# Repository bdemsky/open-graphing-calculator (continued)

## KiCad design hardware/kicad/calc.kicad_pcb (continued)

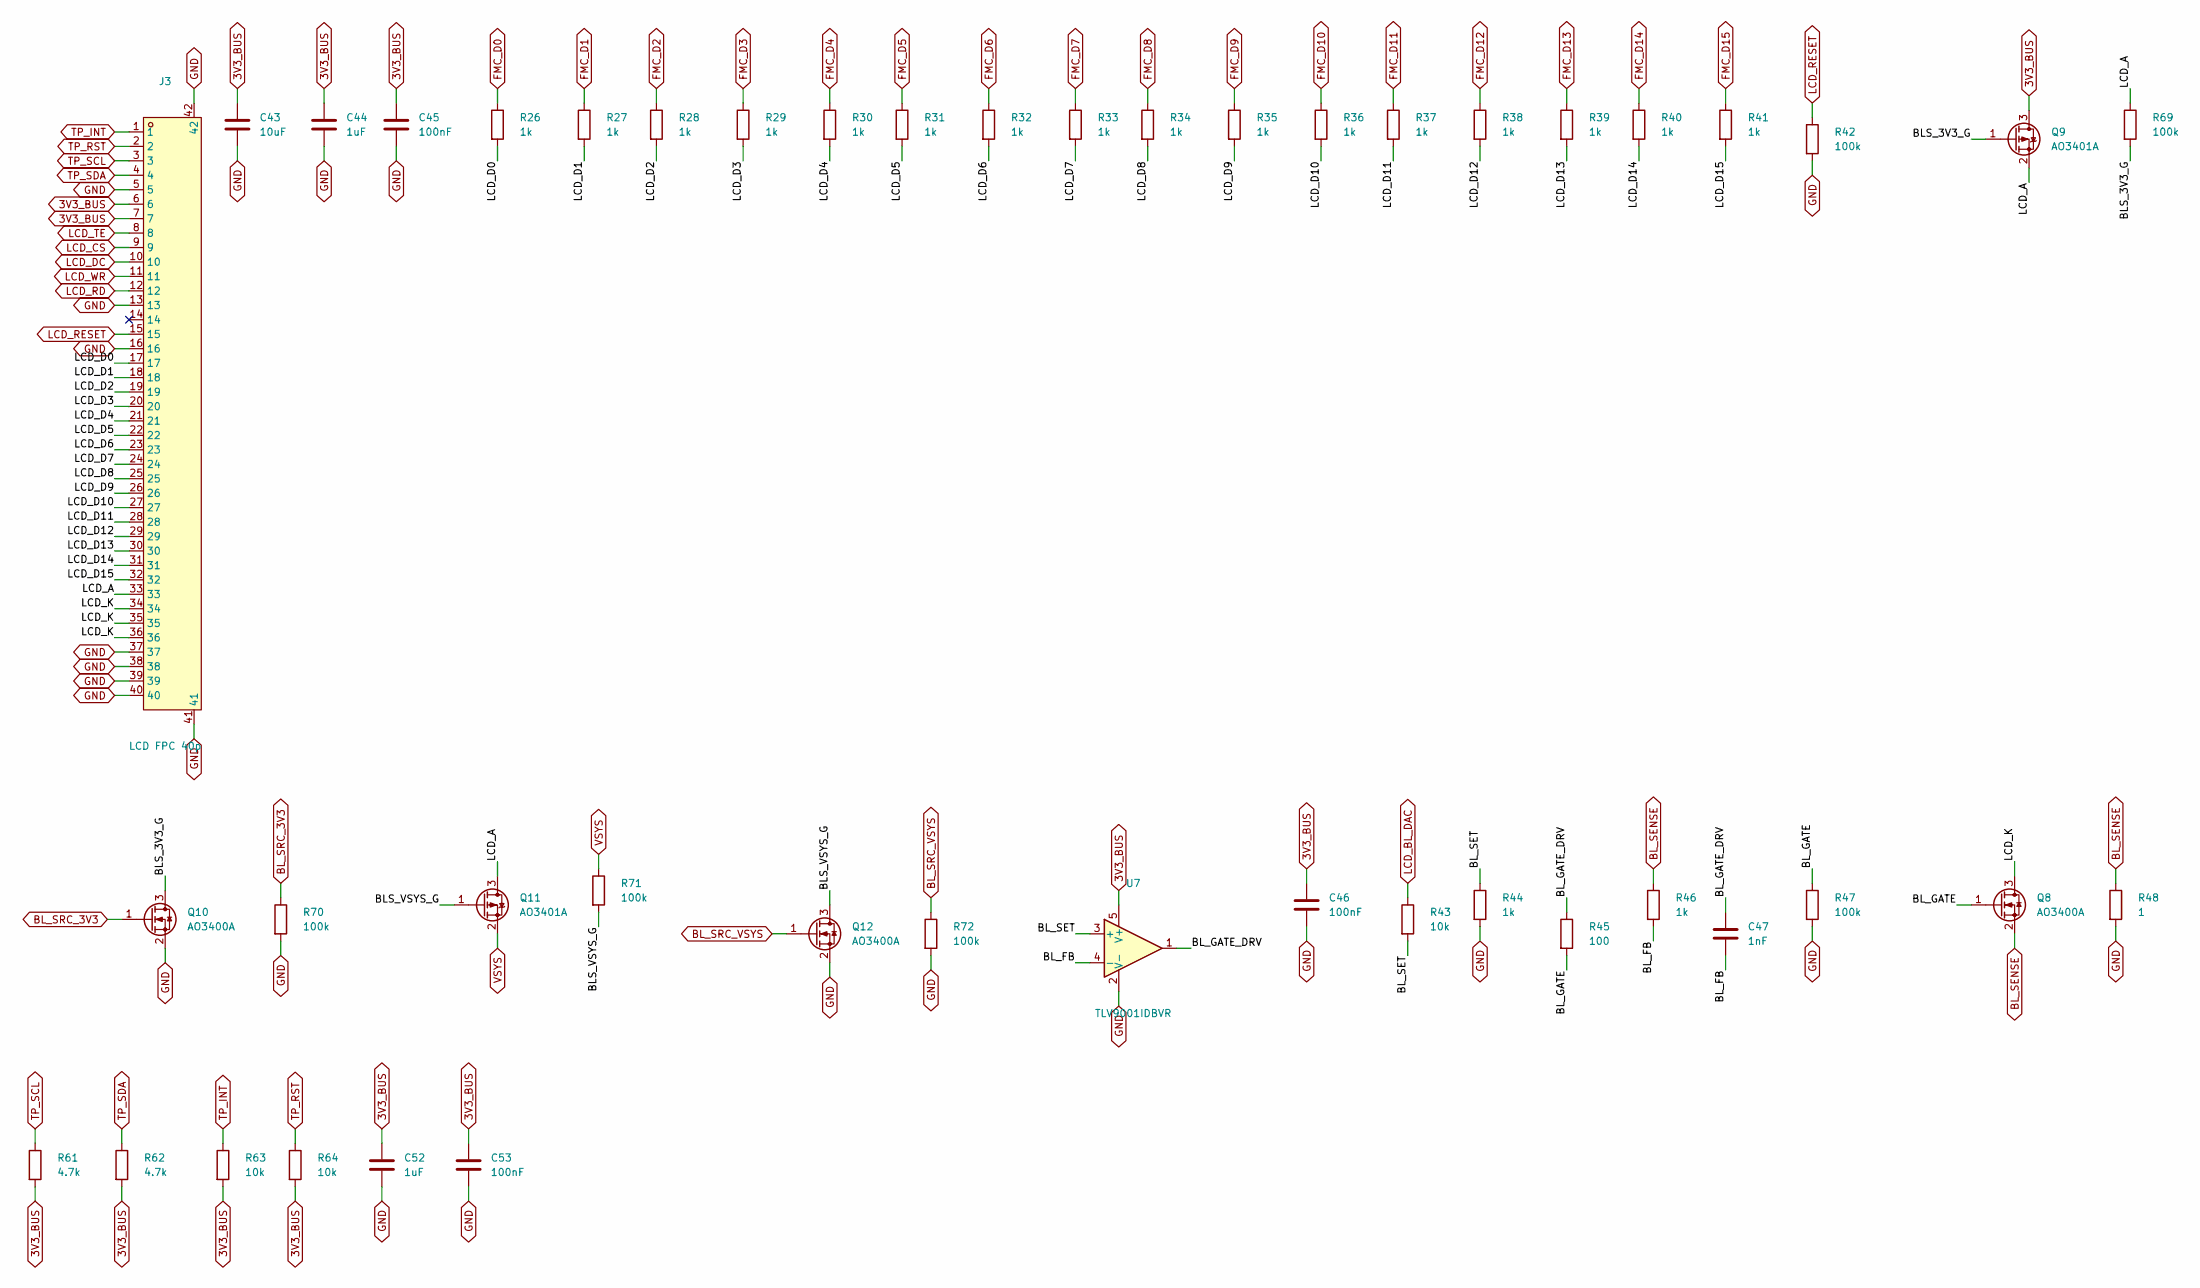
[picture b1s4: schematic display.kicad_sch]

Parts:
C43: 10uF; C_0603_1608Metric; LCSC C19702
C44, C52: 1uF; C_0402_1005Metric; LCSC C52923
C45, C46, C53: 100nF; C_0402_1005Metric; LCSC C307331
C47: 1nF; C_0402_1005Metric; LCSC C1523
J3: LCD FPC 40p; FPC-SMD_P0.50-40P_QCHF-SM-H2.0; LCSC C262686
Q8, Q10, Q12: AO3400A; SOT-23; LCSC C20917
Q9, Q11: AO3401A; SOT-23; LCSC C15127
R26, R27, R28, R29, R30, R31, R32, R33, R34, R35, R36, R37, R38, R39, R40, R41, R44, R46: 1k; R_0402_1005Metric; LCSC C11702
R42, R47, R69, R70, R71, R72: 100k; R_0402_1005Metric; LCSC C25741
R43, R63, R64: 10k; R_0402_1005Metric; LCSC C25744
R45: 100; R_0402_1005Metric; LCSC C25076
R48: 1; R_0603_1608Metric; LCSC C22936
R61, R62: 4.7k; R_0402_1005Metric; LCSC C25900
U7: TLV9001IDBVR; SOT-23-5; LCSC C398363

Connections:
3V3_BUS: C43.1, C44.1, C45.1, C46.1, C52.1, C53.1, J3.6, J3.7, Q9.3 (D), R61.2, R62.2, R63.2, R64.2, U7.5 (V+); also elsewhere on the board
/Display/BLS_3V3_G: Q9.1 (G), Q10.3 (D), R69.2
/Display/BLS_VSYS_G: Q11.1 (G), Q12.3 (D), R71.2
/Display/BL_FB: C47.2, R46.2, U7.4 (-)
/Display/BL_GATE: Q8.1 (G), R45.2, R47.1
/Display/BL_GATE_DRV: C47.1, R45.1, U7.1
/Display/BL_SET: R43.2, R44.1, U7.3 (+)
/Display/LCD_A: J3.33, Q9.2 (S), Q11.3 (D), R69.1
/Display/LCD_D0: J3.17, R26.2
/Display/LCD_D1: J3.18, R27.2
/Display/LCD_D2: J3.19, R28.2
/Display/LCD_D3: J3.20, R29.2
/Display/LCD_D4: J3.21, R30.2
/Display/LCD_D5: J3.22, R31.2
/Display/LCD_D6: J3.23, R32.2
/Display/LCD_D7: J3.24, R33.2
/Display/LCD_D8: J3.25, R34.2
/Display/LCD_D9: J3.26, R35.2
/Display/LCD_D10: J3.27, R36.2
/Display/LCD_D11: J3.28, R37.2
/Display/LCD_D12: J3.29, R38.2
/Display/LCD_D13: J3.30, R39.2
/Display/LCD_D14: J3.31, R40.2
/Display/LCD_D15: J3.32, R41.2
/Display/LCD_K: J3.34, J3.35, J3.36, Q8.3 (D)
BL_SENSE: Q8.2 (S), R46.1, R48.1; also elsewhere on the board
BL_SRC_3V3: Q10.1 (G), R70.1; also elsewhere on the board
BL_SRC_VSYS: Q12.1 (G), R72.1; also elsewhere on the board
FMC_D0: R26.1; also elsewhere on the board
FMC_D1: R27.1; also elsewhere on the board
FMC_D2: R28.1; also elsewhere on the board
FMC_D3: R29.1; also elsewhere on the board
FMC_D4: R30.1; also elsewhere on the board
FMC_D5: R31.1; also elsewhere on the board
FMC_D6: R32.1; also elsewhere on the board
FMC_D7: R33.1; also elsewhere on the board
FMC_D8: R34.1; also elsewhere on the board
FMC_D9: R35.1; also elsewhere on the board
FMC_D10: R36.1; also elsewhere on the board
FMC_D11: R37.1; also elsewhere on the board
FMC_D12: R38.1; also elsewhere on the board
FMC_D13: R39.1; also elsewhere on the board
FMC_D14: R40.1; also elsewhere on the board
FMC_D15: R41.1; also elsewhere on the board
GND: C43.2, C44.2, C45.2, C46.2, C52.2, C53.2, J3.5, J3.13, J3.16, J3.37, J3.38, J3.39, J3.40, J3.41, J3.42, Q10.2 (S), Q12.2 (S), R42.2, R44.2, R47.2, R48.2, R70.2, R72.2, U7.2 (V-); also elsewhere on the board
LCD_BL_DAC: R43.1; also elsewhere on the board
LCD_CS: J3.9; also elsewhere on the board
LCD_DC: J3.10; also elsewhere on the board
LCD_RD: J3.12; also elsewhere on the board
LCD_RESET: J3.15, R42.1; also elsewhere on the board
LCD_TE: J3.8; also elsewhere on the board
LCD_WR: J3.11; also elsewhere on the board
TP_INT: J3.1, R63.1; also elsewhere on the board
TP_RST: J3.2, R64.1; also elsewhere on the board
TP_SCL: J3.3, R61.1; also elsewhere on the board
TP_SDA: J3.4, R62.1; also elsewhere on the board
VSYS: Q11.2 (S), R71.1; also elsewhere on the board

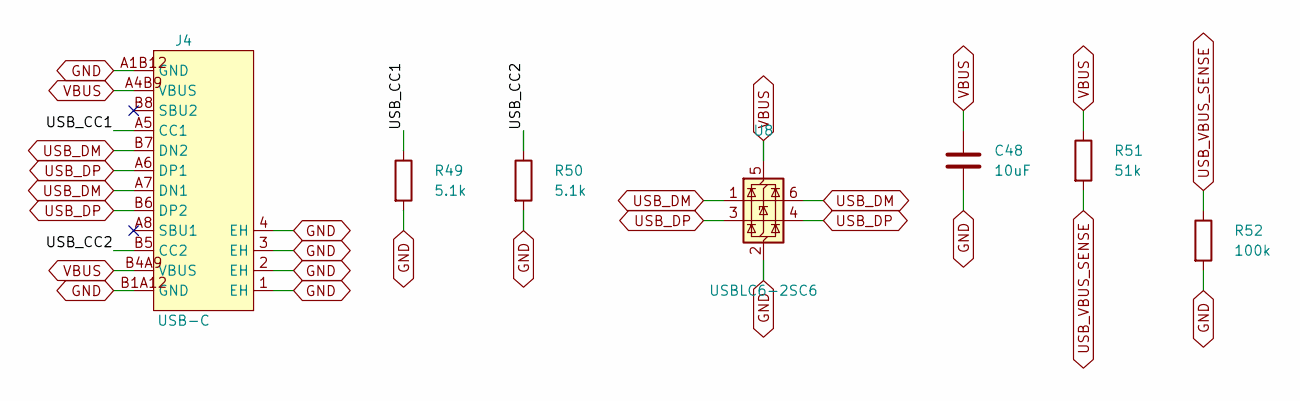
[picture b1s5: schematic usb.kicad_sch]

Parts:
C48: 10uF; C_0603_1608Metric; LCSC C96446
J4: USB-C; USB-C_SMD-TYPE-C-31-M-12_1; LCSC C165948
R49, R50: 5.1k; R_0402_1005Metric; LCSC C25905
R51: 51k; R_0402_1005Metric; LCSC C25794
R52: 100k; R_0402_1005Metric; LCSC C25741
U8: USBLC6-2SC6; SOT-23-6; LCSC C7519

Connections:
/USB/USB_CC1: J4.A5 (CC1), R49.1
/USB/USB_CC2: J4.B5 (CC2), R50.1
GND: C48.2, J4.1 (EH), J4.2 (EH), J4.3 (EH), J4.4 (EH), J4.A1B12 (GND), J4.B1A12 (GND), R49.2, R50.2, R52.2, U8.2 (GND); also elsewhere on the board
USB_DM: J4.A7 (DN1), J4.B7 (DN2), U8.1 (I/O1), U8.6 (I/O1); also elsewhere on the board
USB_DP: J4.A6 (DP1), J4.B6 (DP2), U8.3 (I/O2), U8.4 (I/O2); also elsewhere on the board
USB_VBUS_SENSE: R51.2, R52.1; also elsewhere on the board
VBUS: C48.1, J4.A4B9 (VBUS), J4.B4A9 (VBUS), R51.1, U8.5 (VBUS); also elsewhere on the board

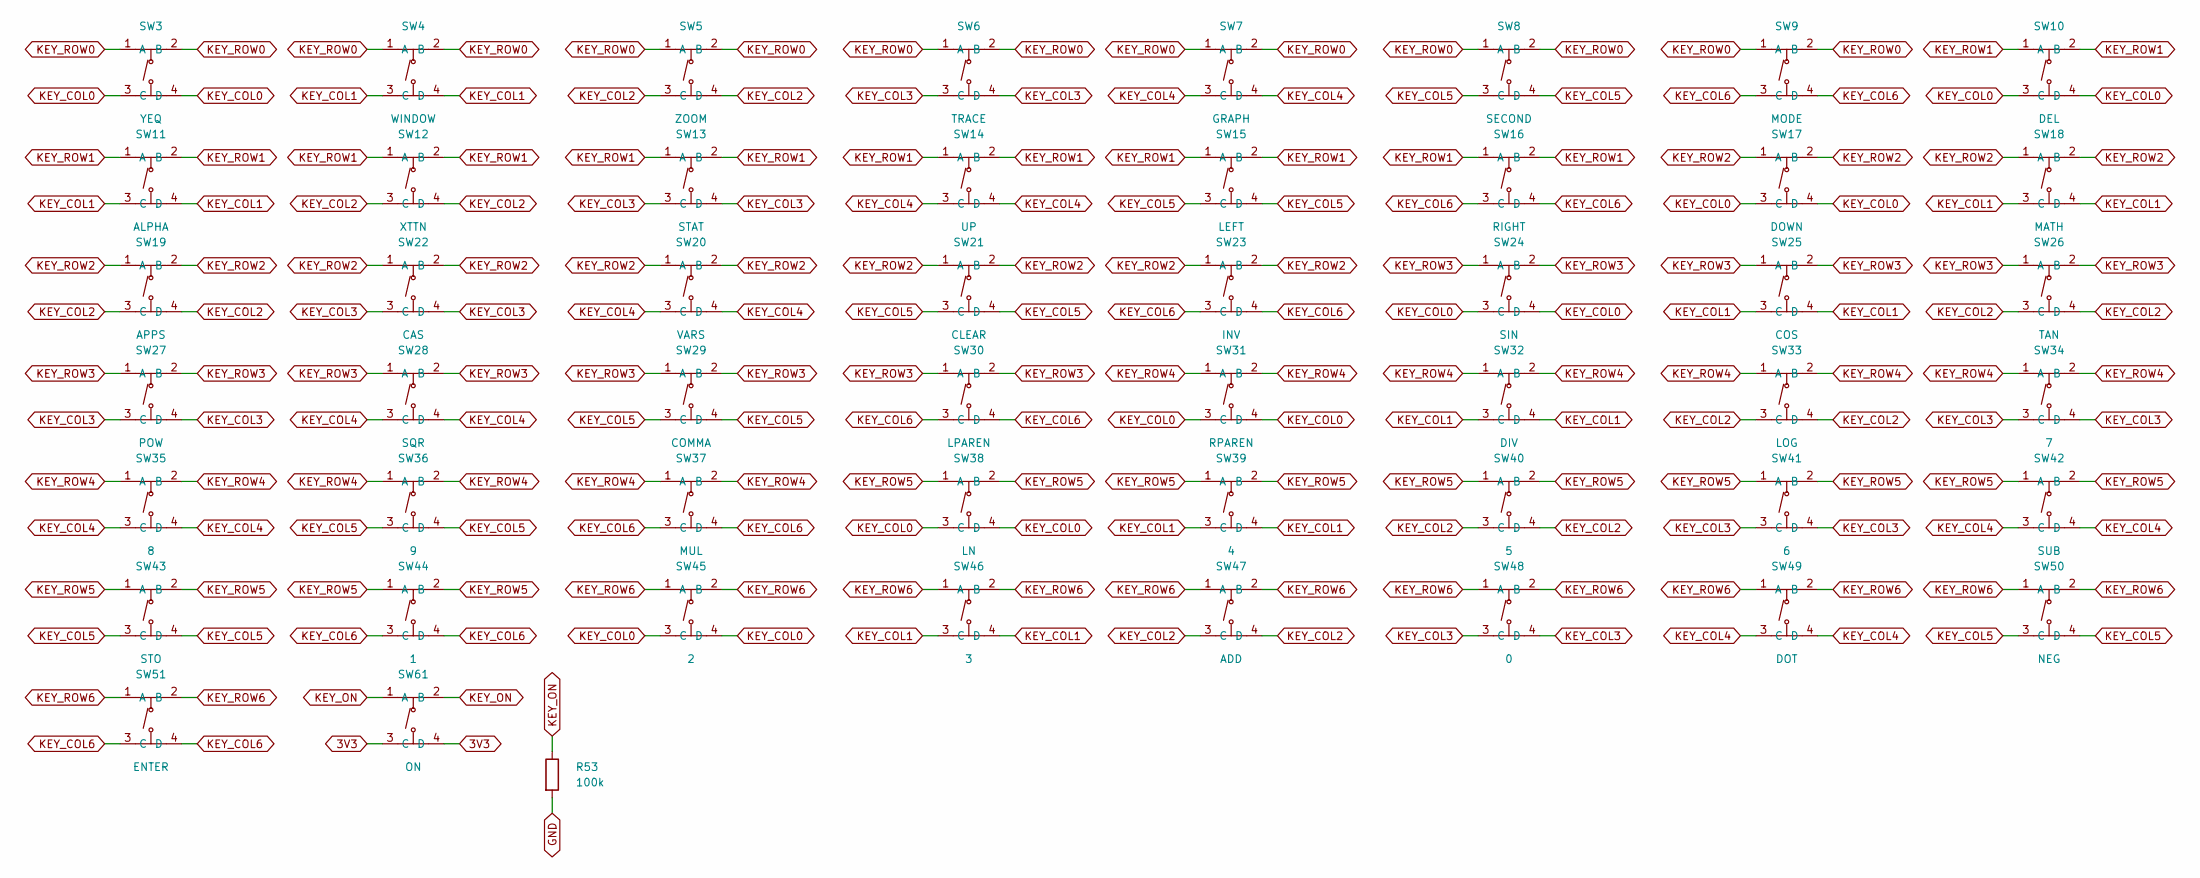
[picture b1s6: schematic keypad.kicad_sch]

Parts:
R53: 100k; R_0402_1005Metric; LCSC C25741
SW3: YEQ; SW-SMD_4P-L5.1-W5.1-P3.70-LS6.5-TL_H1.5; LCSC C318884
SW4: WINDOW; SW-SMD_4P-L5.1-W5.1-P3.70-LS6.5-TL_H1.5; LCSC C318884
SW5: ZOOM; SW-SMD_4P-L5.1-W5.1-P3.70-LS6.5-TL_H1.5; LCSC C318884
SW6: TRACE; SW-SMD_4P-L5.1-W5.1-P3.70-LS6.5-TL_H1.5; LCSC C318884
SW7: GRAPH; SW-SMD_4P-L5.1-W5.1-P3.70-LS6.5-TL_H1.5; LCSC C318884
SW8: SECOND; SW-SMD_4P-L5.1-W5.1-P3.70-LS6.5-TL_H1.5; LCSC C318884
SW9: MODE; SW-SMD_4P-L5.1-W5.1-P3.70-LS6.5-TL_H1.5; LCSC C318884
SW10: DEL; SW-SMD_4P-L5.1-W5.1-P3.70-LS6.5-TL_H1.5; LCSC C318884
SW11: ALPHA; SW-SMD_4P-L5.1-W5.1-P3.70-LS6.5-TL_H1.5; LCSC C318884
SW12: XTTN; SW-SMD_4P-L5.1-W5.1-P3.70-LS6.5-TL_H1.5; LCSC C318884
SW13: STAT; SW-SMD_4P-L5.1-W5.1-P3.70-LS6.5-TL_H1.5; LCSC C318884
SW14: UP; SW-SMD_4P-L5.1-W5.1-P3.70-LS6.5-TL_H1.5; LCSC C318884
SW15: LEFT; SW-SMD_4P-L5.1-W5.1-P3.70-LS6.5-TL_H1.5; LCSC C318884
SW16: RIGHT; SW-SMD_4P-L5.1-W5.1-P3.70-LS6.5-TL_H1.5; LCSC C318884
SW17: DOWN; SW-SMD_4P-L5.1-W5.1-P3.70-LS6.5-TL_H1.5; LCSC C318884
SW18: MATH; SW-SMD_4P-L5.1-W5.1-P3.70-LS6.5-TL_H1.5; LCSC C318884
SW19: APPS; SW-SMD_4P-L5.1-W5.1-P3.70-LS6.5-TL_H1.5; LCSC C318884
SW20: VARS; SW-SMD_4P-L5.1-W5.1-P3.70-LS6.5-TL_H1.5; LCSC C318884
SW21: CLEAR; SW-SMD_4P-L5.1-W5.1-P3.70-LS6.5-TL_H1.5; LCSC C318884
SW22: CAS; SW-SMD_4P-L5.1-W5.1-P3.70-LS6.5-TL_H1.5; LCSC C318884
SW23: INV; SW-SMD_4P-L5.1-W5.1-P3.70-LS6.5-TL_H1.5; LCSC C318884
SW24: SIN; SW-SMD_4P-L5.1-W5.1-P3.70-LS6.5-TL_H1.5; LCSC C318884
SW25: COS; SW-SMD_4P-L5.1-W5.1-P3.70-LS6.5-TL_H1.5; LCSC C318884
SW26: TAN; SW-SMD_4P-L5.1-W5.1-P3.70-LS6.5-TL_H1.5; LCSC C318884
SW27: POW; SW-SMD_4P-L5.1-W5.1-P3.70-LS6.5-TL_H1.5; LCSC C318884
SW28: SQR; SW-SMD_4P-L5.1-W5.1-P3.70-LS6.5-TL_H1.5; LCSC C318884
SW29: COMMA; SW-SMD_4P-L5.1-W5.1-P3.70-LS6.5-TL_H1.5; LCSC C318884
SW30: LPAREN; SW-SMD_4P-L5.1-W5.1-P3.70-LS6.5-TL_H1.5; LCSC C318884
SW31: RPAREN; SW-SMD_4P-L5.1-W5.1-P3.70-LS6.5-TL_H1.5; LCSC C318884
SW32: DIV; SW-SMD_4P-L5.1-W5.1-P3.70-LS6.5-TL_H1.5; LCSC C318884
SW33: LOG; SW-SMD_4P-L5.1-W5.1-P3.70-LS6.5-TL_H1.5; LCSC C318884
SW34: 7; SW-SMD_4P-L5.1-W5.1-P3.70-LS6.5-TL_H1.5; LCSC C318884
SW35: 8; SW-SMD_4P-L5.1-W5.1-P3.70-LS6.5-TL_H1.5; LCSC C318884
SW36: 9; SW-SMD_4P-L5.1-W5.1-P3.70-LS6.5-TL_H1.5; LCSC C318884
SW37: MUL; SW-SMD_4P-L5.1-W5.1-P3.70-LS6.5-TL_H1.5; LCSC C318884
SW38: LN; SW-SMD_4P-L5.1-W5.1-P3.70-LS6.5-TL_H1.5; LCSC C318884
SW39: 4; SW-SMD_4P-L5.1-W5.1-P3.70-LS6.5-TL_H1.5; LCSC C318884
SW40: 5; SW-SMD_4P-L5.1-W5.1-P3.70-LS6.5-TL_H1.5; LCSC C318884
SW41: 6; SW-SMD_4P-L5.1-W5.1-P3.70-LS6.5-TL_H1.5; LCSC C318884
SW42: SUB; SW-SMD_4P-L5.1-W5.1-P3.70-LS6.5-TL_H1.5; LCSC C318884
SW43: STO; SW-SMD_4P-L5.1-W5.1-P3.70-LS6.5-TL_H1.5; LCSC C318884
SW44: 1; SW-SMD_4P-L5.1-W5.1-P3.70-LS6.5-TL_H1.5; LCSC C318884
SW45: 2; SW-SMD_4P-L5.1-W5.1-P3.70-LS6.5-TL_H1.5; LCSC C318884
SW46: 3; SW-SMD_4P-L5.1-W5.1-P3.70-LS6.5-TL_H1.5; LCSC C318884
SW47: ADD; SW-SMD_4P-L5.1-W5.1-P3.70-LS6.5-TL_H1.5; LCSC C318884
SW48: 0; SW-SMD_4P-L5.1-W5.1-P3.70-LS6.5-TL_H1.5; LCSC C318884
SW49: DOT; SW-SMD_4P-L5.1-W5.1-P3.70-LS6.5-TL_H1.5; LCSC C318884
SW50: NEG; SW-SMD_4P-L5.1-W5.1-P3.70-LS6.5-TL_H1.5; LCSC C318884
SW51: ENTER; SW-SMD_4P-L5.1-W5.1-P3.70-LS6.5-TL_H1.5; LCSC C318884
SW61: ON; SW-SMD_4P-L5.1-W5.1-P3.70-LS6.5-TL_H1.5; LCSC C318884

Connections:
3V3: SW61.3 (C), SW61.4 (D); also elsewhere on the board
GND: R53.2; also elsewhere on the board
KEY_COL0: SW3.3 (C), SW3.4 (D), SW10.3 (C), SW10.4 (D), SW17.3 (C), SW17.4 (D), SW24.3 (C), SW24.4 (D), SW31.3 (C), SW31.4 (D), SW38.3 (C), SW38.4 (D), SW45.3 (C), SW45.4 (D); also elsewhere on the board
KEY_COL1: SW4.3 (C), SW4.4 (D), SW11.3 (C), SW11.4 (D), SW18.3 (C), SW18.4 (D), SW25.3 (C), SW25.4 (D), SW32.3 (C), SW32.4 (D), SW39.3 (C), SW39.4 (D), SW46.3 (C), SW46.4 (D); also elsewhere on the board
KEY_COL2: SW5.3 (C), SW5.4 (D), SW12.3 (C), SW12.4 (D), SW19.3 (C), SW19.4 (D), SW26.3 (C), SW26.4 (D), SW33.3 (C), SW33.4 (D), SW40.3 (C), SW40.4 (D), SW47.3 (C), SW47.4 (D); also elsewhere on the board
KEY_COL3: SW6.3 (C), SW6.4 (D), SW13.3 (C), SW13.4 (D), SW22.3 (C), SW22.4 (D), SW27.3 (C), SW27.4 (D), SW34.3 (C), SW34.4 (D), SW41.3 (C), SW41.4 (D), SW48.3 (C), SW48.4 (D); also elsewhere on the board
KEY_COL4: SW7.3 (C), SW7.4 (D), SW14.3 (C), SW14.4 (D), SW20.3 (C), SW20.4 (D), SW28.3 (C), SW28.4 (D), SW35.3 (C), SW35.4 (D), SW42.3 (C), SW42.4 (D), SW49.3 (C), SW49.4 (D); also elsewhere on the board
KEY_COL5: SW8.3 (C), SW8.4 (D), SW15.3 (C), SW15.4 (D), SW21.3 (C), SW21.4 (D), SW29.3 (C), SW29.4 (D), SW36.3 (C), SW36.4 (D), SW43.3 (C), SW43.4 (D), SW50.3 (C), SW50.4 (D); also elsewhere on the board
KEY_COL6: SW9.3 (C), SW9.4 (D), SW16.3 (C), SW16.4 (D), SW23.3 (C), SW23.4 (D), SW30.3 (C), SW30.4 (D), SW37.3 (C), SW37.4 (D), SW44.3 (C), SW44.4 (D), SW51.3 (C), SW51.4 (D); also elsewhere on the board
KEY_ON: R53.1, SW61.1 (A), SW61.2 (B); also elsewhere on the board
KEY_ROW0: SW3.1 (A), SW3.2 (B), SW4.1 (A), SW4.2 (B), SW5.1 (A), SW5.2 (B), SW6.1 (A), SW6.2 (B), SW7.1 (A), SW7.2 (B), SW8.1 (A), SW8.2 (B), SW9.1 (A), SW9.2 (B); also elsewhere on the board
KEY_ROW1: SW10.1 (A), SW10.2 (B), SW11.1 (A), SW11.2 (B), SW12.1 (A), SW12.2 (B), SW13.1 (A), SW13.2 (B), SW14.1 (A), SW14.2 (B), SW15.1 (A), SW15.2 (B), SW16.1 (A), SW16.2 (B); also elsewhere on the board
KEY_ROW2: SW17.1 (A), SW17.2 (B), SW18.1 (A), SW18.2 (B), SW19.1 (A), SW19.2 (B), SW20.1 (A), SW20.2 (B), SW21.1 (A), SW21.2 (B), SW22.1 (A), SW22.2 (B), SW23.1 (A), SW23.2 (B); also elsewhere on the board
KEY_ROW3: SW24.1 (A), SW24.2 (B), SW25.1 (A), SW25.2 (B), SW26.1 (A), SW26.2 (B), SW27.1 (A), SW27.2 (B), SW28.1 (A), SW28.2 (B), SW29.1 (A), SW29.2 (B), SW30.1 (A), SW30.2 (B); also elsewhere on the board
KEY_ROW4: SW31.1 (A), SW31.2 (B), SW32.1 (A), SW32.2 (B), SW33.1 (A), SW33.2 (B), SW34.1 (A), SW34.2 (B), SW35.1 (A), SW35.2 (B), SW36.1 (A), SW36.2 (B), SW37.1 (A), SW37.2 (B); also elsewhere on the board
KEY_ROW5: SW38.1 (A), SW38.2 (B), SW39.1 (A), SW39.2 (B), SW40.1 (A), SW40.2 (B), SW41.1 (A), SW41.2 (B), SW42.1 (A), SW42.2 (B), SW43.1 (A), SW43.2 (B), SW44.1 (A), SW44.2 (B); also elsewhere on the board
KEY_ROW6: SW45.1 (A), SW45.2 (B), SW46.1 (A), SW46.2 (B), SW47.1 (A), SW47.2 (B), SW48.1 (A), SW48.2 (B), SW49.1 (A), SW49.2 (B), SW50.1 (A), SW50.2 (B), SW51.1 (A), SW51.2 (B); also elsewhere on the board

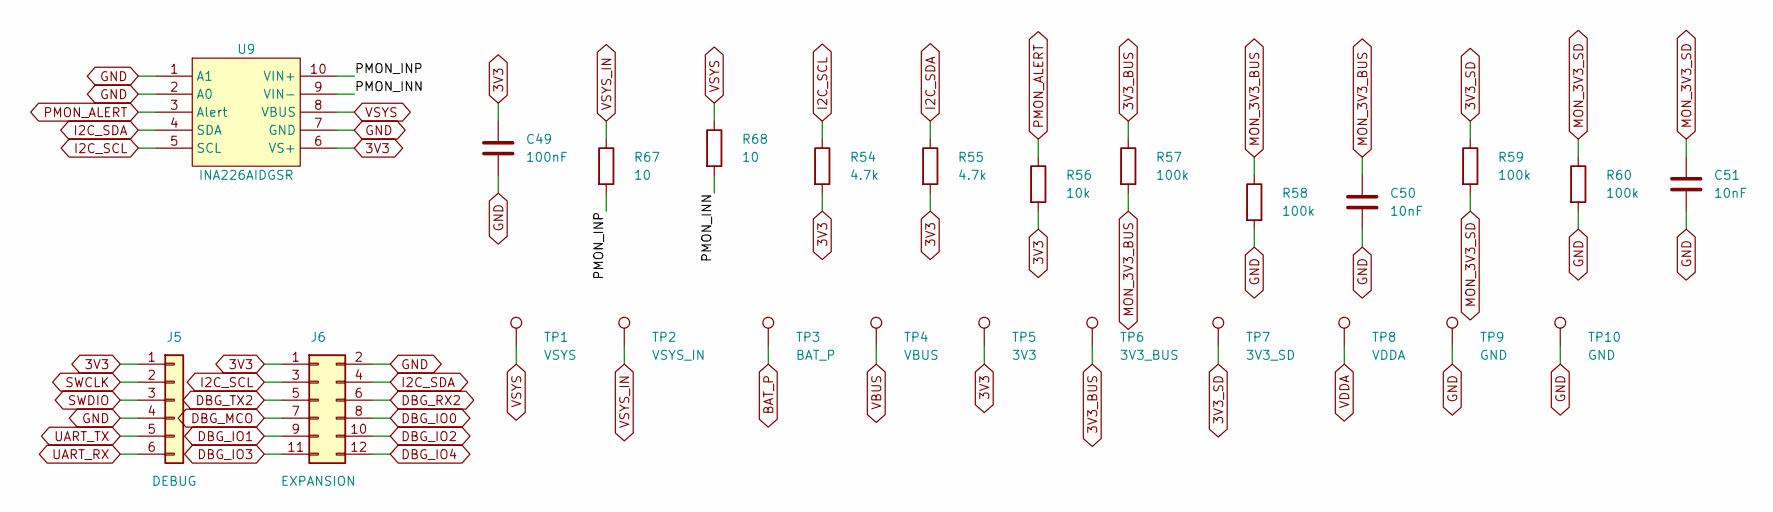
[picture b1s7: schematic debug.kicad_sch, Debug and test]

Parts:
C49: 100nF; C_0402_1005Metric; LCSC C307331
C50, C51: 10nF; C_0402_1005Metric; LCSC C15195
J5: DEBUG; PinHeader_1x06_P2.54mm_Vertical; LCSC C492405
J6: EXPANSION; PinHeader_2x06_P2.54mm_Vertical; LCSC C492423
R54, R55: 4.7k; R_0402_1005Metric; LCSC C25900
R56: 10k; R_0402_1005Metric; LCSC C25744
R57, R58, R59, R60: 100k; R_0402_1005Metric; LCSC C25741
R67, R68: 10; R_0402_1005Metric; LCSC C25077
TP1: VSYS; TestPoint_Pad_D1.5mm
TP2: VSYS_IN; TestPoint_Pad_D1.5mm
TP3: BAT_P; TestPoint_Pad_D1.5mm
TP4: VBUS; TestPoint_Pad_D1.5mm
TP5: 3V3; TestPoint_Pad_D1.5mm
TP6: 3V3_BUS; TestPoint_Pad_D1.5mm
TP7: 3V3_SD; TestPoint_Pad_D1.5mm
TP8: VDDA; TestPoint_Pad_D1.5mm
TP9, TP10: GND; TestPoint_Pad_D1.5mm
U9: INA226AIDGSR; MSOP-10_L3.0-W3.0-P0.50-LS5.0-BL; LCSC C49851

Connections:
3V3: C49.1, J5.1, J6.1, R54.2, R55.2, R56.2, TP5.1, U9.6 (VS+); also elsewhere on the board
3V3_BUS: R57.1, TP6.1; also elsewhere on the board
3V3_SD: R59.1, TP7.1; also elsewhere on the board
/Debug and test/PMON_INN: R68.2, U9.9 (VIN-)
/Debug and test/PMON_INP: R67.2, U9.10 (VIN+)
BAT_P: TP3.1; also elsewhere on the board
DBG_IO0: J6.8; also elsewhere on the board
DBG_IO1: J6.9; also elsewhere on the board
DBG_IO2: J6.10; also elsewhere on the board
DBG_IO3: J6.11; also elsewhere on the board
DBG_IO4: J6.12; also elsewhere on the board
DBG_MCO: J6.7; also elsewhere on the board
DBG_RX2: J6.6; also elsewhere on the board
DBG_TX2: J6.5; also elsewhere on the board
GND: C49.2, C50.2, C51.2, J5.4, J6.2, R58.2, R60.2, TP9.1, TP10.1, U9.1 (A1), U9.2 (A0), U9.7 (GND); also elsewhere on the board
I2C_SCL: J6.3, R54.1, U9.5 (SCL); also elsewhere on the board
I2C_SDA: J6.4, R55.1, U9.4 (SDA); also elsewhere on the board
MON_3V3_BUS: C50.1, R57.2, R58.1; also elsewhere on the board
MON_3V3_SD: C51.1, R59.2, R60.1; also elsewhere on the board
PMON_ALERT: R56.1, U9.3 (Alert); also elsewhere on the board
SWCLK: J5.2; also elsewhere on the board
SWDIO: J5.3; also elsewhere on the board
UART_RX: J5.6; also elsewhere on the board
UART_TX: J5.5; also elsewhere on the board
VBUS: TP4.1; also elsewhere on the board
VDDA: TP8.1; also elsewhere on the board
VSYS: R68.1, TP1.1, U9.8 (VBUS); also elsewhere on the board
VSYS_IN: R67.1, TP2.1; also elsewhere on the board

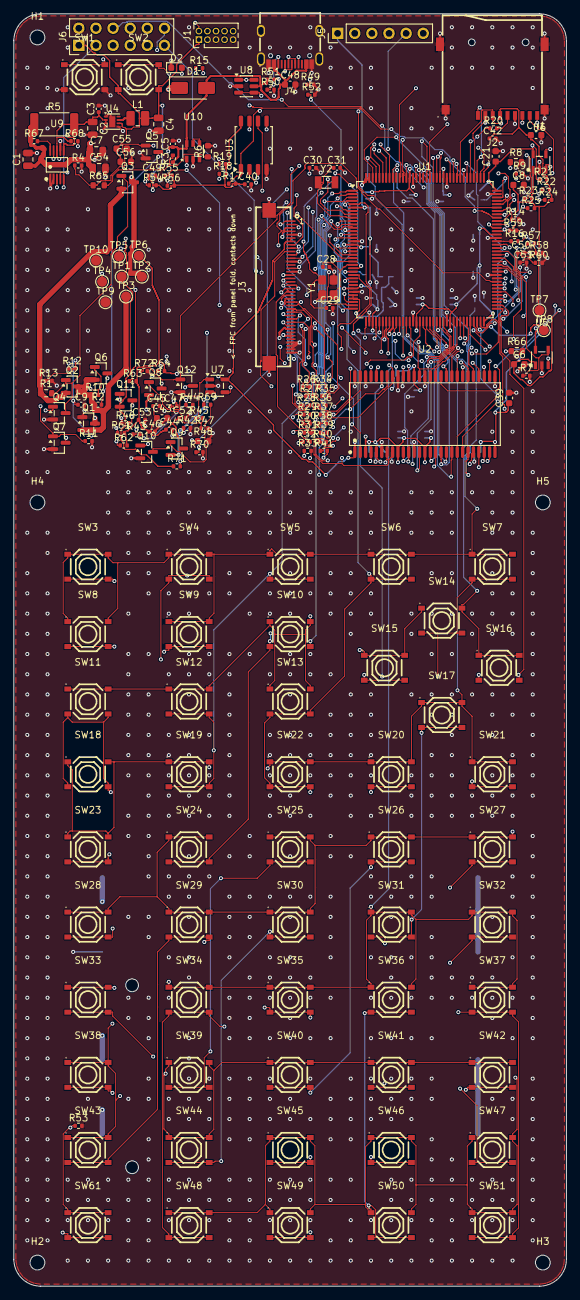
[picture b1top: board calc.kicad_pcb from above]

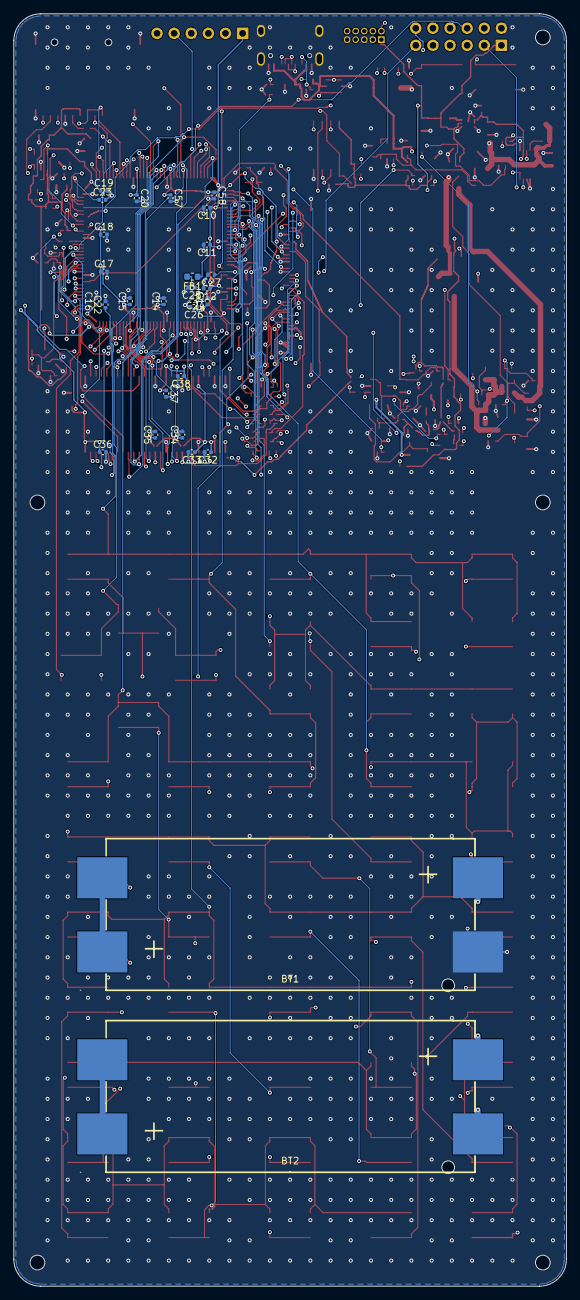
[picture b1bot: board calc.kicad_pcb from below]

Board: 4 copper layers, 82.0 x 188.8 mm, 233 parts (29 on the bottom side), 170 nets.

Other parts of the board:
H1, H2, H3, H4, H5: MountingHole_2.2mm_M2

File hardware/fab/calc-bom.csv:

Comment,Designator,Footprint,LCSC Part #
2xAAA,"BT1,BT2",BAT-SMD_BH-AAA-B5AA001,C964881
22uF,"C1,C4,C7,C54",C_0805_2012Metric,C45783
100nF,"C10,C11,C12,C13,C14,C15,C16,C17,C18,C19,C20,C25,C26,C27,C32,C33,C34,C35,C36,C37,C38,C57,C58,C3,C5,C9,C40,C42,C45,C46,C49,C53",C_0402_1005Metric,C307331
10uF,C2,C_0805_2012Metric,C15850
4.7uF,C21,C_0603_1608Metric,C19666
2.2uF,"C22,C23",C_0402_1005Metric,C12530
1uF,"C24,C44,C52",C_0402_1005Metric,C52923
15pF,"C28,C29",C_0402_1005Metric,C1548
10pF,"C30,C31",C_0402_1005Metric,C32949
1nF,C47,C_0402_1005Metric,C1523
10uF,C48,C_0603_1608Metric,C96446
10nF,"C50,C51",C_0402_1005Metric,C15195
10uF,"C6,C8,C39,C41,C43,C55,C56",C_0603_1608Metric,C19702
M7,D1,D_SMA,C95872
red,D2,LED_0603_1608Metric,C2286
120R@100MHz,FB1,L_0603_1608Metric,C14709
SWD,J1,PinHeader_2x05_P1.27mm_Vertical,C22438120
microSD,J2,TF-SMD_TF-01A,C91145
LCD FPC 40p,J3,FPC-SMD_P0.50-40P_QCHF-SM-H2.0,C262686
USB-C,J4,USB-C_SMD-TYPE-C-31-M-12_1,C165948
DEBUG,J5,PinHeader_1x06_P2.54mm_Vertical,C492405
EXPANSION,J6,PinHeader_2x06_P2.54mm_Vertical,C492423
2.2uH,L1,L_1008_2520Metric,C5832372
AO3401A,"Q1,Q2,Q3,Q6,Q9,Q11",SOT-23,C15127
AO3400A,"Q4,Q5,Q7,Q8,Q10,Q12",SOT-23,C20917
2M,R1,R_0603_1608Metric,C22976
10k,"R14,R17,R18,R19,R43,R56,R63,R64",R_0402_1005Metric,C25744
1k,"R15,R26,R27,R28,R29,R30,R31,R32,R33,R34,R35,R36,R37,R38,R39,R40,R41,R44,R46",R_0402_1005Metric,C11702
22,"R16,R20",R_0402_1005Metric,C25092
47k,"R2,R13,R21,R22,R23,R24,R25",R_0402_1005Metric,C25792
200k,R3,R_0402_1005Metric,C25764
100k,"R4,R7,R9,R10,R11,R12,R42,R47,R52,R53,R57,R58,R59,R60,R69,R70,R71,R72",R_0402_1005Metric,C25741
100,R45,R_0402_1005Metric,C25076
1,R48,R_0603_1608Metric,C22936
5.1k,"R49,R50",R_0402_1005Metric,C25905
0.1 1%,R5,R_2512_6332Metric,C160587
51k,R51,R_0402_1005Metric,C25794
4.7k,"R54,R55,R61,R62",R_0402_1005Metric,C25900
82k,R6,R_0603_1608Metric,C23254
10M,R65,R_0603_1608Metric,C7250
10,"R67,R68",R_0402_1005Metric,C25077
13k,"R8,R66",R_0603_1608Metric,C22797
SW-SMD_4P-L5.1-W5.1-P3.70-LS6.5-TL_H1.5,"SW1,SW2,SW3,SW4,SW5,SW6,SW7,SW8,SW9,SW10,SW11,SW12,SW13,SW14,SW15,SW16,SW17,SW18,SW19,SW20,SW21,SW22,SW23,SW24,SW25,SW26,SW27,SW28,SW29,SW30,SW31,SW32,SW33,SW34,SW35,SW36,SW37,SW38,SW39,SW40,SW41,SW42,SW43,SW44,SW45,SW46,SW47,SW48,SW49,SW50,SW51,SW61",SW-SMD_4P-L5.1-W5.1-P3.70-LS6.5-TL_H1.5,C318884
STM32H743ZGT6,U1,LQFP-144_20x20mm_P0.5mm,C730184
TLV3012BIDBVR,U10,SOT-23-6_L2.9-W1.7-P0.95-LS2.8-BL,C20345924
W9825G6KH-6,U2,TSOP-54_L22.2-W10.2-P0.80-LS11.8-BL,C62246
W25Q128JVSIQ,U3,SOIC-8_5.3x5.3mm_P1.27mm,C97521
TPS62162DSGR,U4,Texas_DSG0008A_WSON-8-1EP_2x2mm_P0.5mm_EP0.9x1.6mm,C40256
SY6280AAC,"U5,U6",SOT-23-5_L3.0-W1.7-P0.95-LS2.8-BL,C55136
TLV9001IDBVR,U7,SOT-23-5,C398363
USBLC6-2SC6,U8,SOT-23-6,C7519
INA226AIDGSR,U9,MSOP-10_L3.0-W3.0-P0.50-LS5.0-BL,C49851
25MHz,Y1,Crystal_SMD_3225-4Pin_3.2x2.5mm,C9006
32.768kHz,Y2,Crystal_SMD_3215-2Pin_3.2x1.5mm,C97604

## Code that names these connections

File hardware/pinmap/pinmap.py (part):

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# plain dict of string tuples)
ASSIGN = {
    # --- Clocks / system ---
    "HSE_IN": ("PH0", "RCC_OSC_IN", "25 MHz crystal"),
    "HSE_OUT": ("PH1", "RCC_OSC_OUT", ""),
    "LSE_IN": ("PC14", "RCC_OSC32_IN", "32.768 kHz crystal"),
    "LSE_OUT": ("PC15", "RCC_OSC32_OUT", ""),
    "SWDIO": ("PA13", "DEBUG_JTMS-SWDIO", ""),
    "SWCLK": ("PA14", "DEBUG_JTCK-SWCLK", ""),
    "SWO": ("PB3", "DEBUG_JTDO-SWO", "optional trace"),
    "UART_TX": ("PA9", "USART1_TX", "debug console"),
    "UART_RX": ("PA10", "USART1_RX", "debug console"),
    "KEY_ON": ("PA0", "PWR_WKUP1", "ON key, wakes from Standby"),
    # --- SDRAM: FMC bank 2 ---
    "FMC_D0": ("PD14", "FMC_D0", ""), "FMC_D1": ("PD15", "FMC_D1", ""),
    "FMC_D2": ("PD0", "FMC_D2", ""), "FMC_D3": ("PD1", "FMC_D3", ""),
    "FMC_D4": ("PE7", "FMC_D4", ""), "FMC_D5": ("PE8", "FMC_D5", ""),
    "FMC_D6": ("PE9", "FMC_D6", ""), "FMC_D7": ("PE10", "FMC_D7", ""),
    "FMC_D8": ("PE11", "FMC_D8", ""), "FMC_D9": ("PE12", "FMC_D9", ""),
    "FMC_D10": ("PE13", "FMC_D10", ""), "FMC_D11": ("PE14", "FMC_D11", ""),
    "FMC_D12": ("PE15", "FMC_D12", ""), "FMC_D13": ("PD8", "FMC_D13", ""),
    "FMC_D14": ("PD9", "FMC_D14", ""), "FMC_D15": ("PD10", "FMC_D15", ""),
    "FMC_A0": ("PF0", "FMC_A0", ""), "FMC_A1": ("PF1", "FMC_A1", ""),
    "FMC_A2": ("PF2", "FMC_A2", ""), "FMC_A3": ("PF3", "FMC_A3", ""),
    "FMC_A4": ("PF4", "FMC_A4", ""), "FMC_A5": ("PF5", "FMC_A5", ""),
    "FMC_A6": ("PF12", "FMC_A6", ""), "FMC_A7": ("PF13", "FMC_A7", ""),
    "FMC_A8": ("PF14", "FMC_A8", ""), "FMC_A9": ("PF15", "FMC_A9", ""),
    "FMC_A10": ("PG0", "FMC_A10", ""), "FMC_A11": ("PG1", "FMC_A11", ""),
    "FMC_A12": ("PG2", "FMC_A12", ""),
    "FMC_BA0": ("PG4", "FMC_A14", "SDRAM BA0 = FMC_A14/BA0"),
    "FMC_BA1": ("PG5", "FMC_A15", "SDRAM BA1 = FMC_A15/BA1"),
    "FMC_NBL0": ("PE0", "FMC_NBL0", "SDRAM LDQM"),
    "FMC_NBL1": ("PE1", "FMC_NBL1", "SDRAM UDQM"),
    "FMC_SDCLK": ("PG8", "FMC_SDCLK", "series 22-33R at MCU"),
    "FMC_SDNCAS": ("PG15", "FMC_SDNCAS", ""),
    "FMC_SDNRAS": ("PF11", "FMC_SDNRAS", ""),
    "FMC_SDNWE": ("PC0", "FMC_SDNWE", ""),
    "FMC_SDCKE1": ("PB5", "FMC_SDCKE1", ""),
    "FMC_SDNE1": ("PB6", "FMC_SDNE1", ""),
    # --- LCD: FMC NOR/SRAM bank 1, 8080 16-bit (shares D0-D15) ---
    "LCD_CS": ("PD7", "FMC_NE1", "CSX"),
    "LCD_RD": ("PD4", "FMC_NOE", "RDX"),
    "LCD_WR": ("PD5", "FMC_NWE", "WRX"),
    "LCD_DC": ("PD11", "FMC_A16", "DCX: 0=cmd, 1=data"),
    "LCD_RESET": ("PD3", "GPIO_Output", "/RES"),
    "LCD_TE": ("PG9", "GPIO_EXTI9", "tearing effect (own EXTI line)"),
    "LCD_BL_DAC": ("PA4", "DAC1_OUT1", "backlight current setpoint"),
    # --- QSPI flash ---
    "QSPI_CLK": ("PB2", "QUADSPI_CLK", ""),
    "QSPI_NCS": ("PG6", "QUADSPI_BK1_NCS", ""),
    "QSPI_IO0": ("PF8", "QUADSPI_BK1_IO0", ""),
    "QSPI_IO1": ("PF9", "QUADSPI_BK1_IO1", ""),
    "QSPI_IO2": ("PF7", "QUADSPI_BK1_IO2", ""),
    "QSPI_IO3": ("PF6", "QUADSPI_BK1_IO3", ""),
    # --- microSD, 4-bit SDMMC1 ---
    "SD_D0": ("PC8", "SDMMC1_D0", ""), "SD_D1": ("PC9", "SDMMC1_D1", ""),
    "SD_D2": ("PC10", "SDMMC1_D2", ""), "SD_D3": ("PC11", "SDMMC1_D3", ""),
    "SD_CK": ("PC12", "SDMMC1_CK", ""), "SD_CMD": ("PD2", "SDMMC1_CMD", ""),
    "SD_DETECT": ("PG7", "GPIO_Input", "card detect switch"),
    # --- USB FS device ---
    "USB_DM": ("PA11", "USB_OTG_FS_DM", ""),
    "USB_DP": ("PA12", "USB_OTG_FS_DP", ""),
    "USB_VBUS_SENSE": ("PA2", "GPIO_Input", "VBUS divider"),
    # --- Power management ---
    "BUS_EN": ("PG3", "GPIO_Output", "3V3_BUS load switch (SDRAM + LCD logic)"),
    "SD_EN": ("PG10", "GPIO_Output", "microSD load switch"),
    "VBAT_SENSE": ("PA3", "ADC1_INP15", "battery divider"),
    "VBAT_SENSE_EN": ("PA1", "GPIO_Output", "enables battery divider"),
    "LED_DEBUG": ("PB8", "GPIO_Output", "bring-up LED"),
    "BL_SRC_VSYS": ("PD6", "GPIO_Output", "backlight anode from VSYS (high = on; 100k pull-down)"),
    "BL_SRC_3V3": ("PC13", "GPIO_Output", "backlight anode from 3V3_BUS (high = on; 100k pull-down = off at reset)"),
    # --- Debug / observability (so the board can be debugged remotely) ---
    "I2C_SCL": ("PB10", "I2C2_SCL", "INA226 power monitor + header"),
    "I2C_SDA": ("PB11", "I2C2_SDA", "INA226 power monitor + header"),
    "PMON_ALERT": ("PF10", "GPIO_EXTI10", "INA226 alert (open drain, own EXTI line)"),
    "MON_3V3_BUS": ("PA6", "ADC1_INP3", "rail monitor, 1:2 divider"),
    "MON_3V3_SD": ("PC4", "ADC1_INP4", "rail monitor, 1:2 divider"),
    "BL_SENSE": ("PC5", "ADC1_INP8", "backlight current, 1 V/A"),
    "DBG_TX2": ("PC6", "USART6_TX", "second UART on expansion header"),
    "DBG_RX2": ("PC7", "USART6_RX", "second UART on expansion header"),
    "DBG_MCO": ("PA8", "RCC_MCO_1", "clock output for measurement"),
    "DBG_IO0": ("PA15", "GPIO_Output", "timing marker"),
    "DBG_IO1": ("PB9", "GPIO_Output", "timing marker"),
    "DBG_IO2": ("PB15", "GPIO_Output", "timing marker"),
    "DBG_IO3": ("PA5", "GPIO_Output", "timing marker"),
    "DBG_IO4": ("PB7", "GPIO_Output", "timing marker"),
    # --- Capacitive touch (FT6236 on the panel's 40-pin FPC, J3 pins 1-4), own I2C bus on
    # 3V3_BUS pull-ups ---
    "TP_SCL": ("PD12", "I2C4_SCL", "touch controller, I2C addr 0x38"),
    "TP_SDA": ("PD13", "I2C4_SDA", "touch controller"),
    "TP_INT": ("PC1", "GPIO_EXTI1", "touch interrupt (own EXTI line)"),
    "TP_RST": ("PA7", "GPIO_Output", "touch reset, active low"),
}

# Keypad: 7 rows (driven) x 7 columns (inputs with pull-ups, EXTI wake) = 49 keys + ON.
# Columns need distinct pin numbers because EXTI lines are shared by number.
KEY_ROWS = ["PG11", "PG12", "PG13", "PG14", "PB0", "PB1", "PB4"]
KEY_COLS = ["PE2", "PE3", "PE4", "PE5", "PE6", "PB12", "PB13"]


def base(name):
    """'PA13 (JTMS/SWDIO)', 'PC14-OSC32_IN', 'PC2_C' -> 'PA13', 'PC14', 'PC2_C'."""
    m = re.match(r"P[A-K]\d+(_C)?", name)
    return m.group(0) if m else name

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    if len(set(col_numbers)) != len(col_numbers):
        errors.append("keypad columns share an EXTI line number")

    # spare I/O pins, ordered by port letter then pin number (PA0, PA1, ..., PB0, ...)
    free = sorted(
        (n for n, (_, t, _) in pins.items() if t == "I/O" and n not in used),
        key=lambda n: (n[1], int(re.sub(r"\D", "", n))),
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
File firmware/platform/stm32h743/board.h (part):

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 * (final hardware: EastRising ER-TFT032IPS-3.2 panel (ST7789, 240x320 IPS) with
 * the ER-TPC032-3.1 capacitive touch panel (FocalTech FT6236 on the LCD's own
 * 40-pin FPC, J3 pins 1-4), shared 3V3_BUS rail for SDRAM + LCD + touch,
 * TE on PG9, PMON_ALERT on PF10).
 *
 * The PIN() table below is the single source of truth for the firmware's
 * GPIO configuration. tools/check_pins.py parses it and checks every entry
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 * USART6, 9/10 QUADSPI, 10 OTG_FS, 12 FMC and SDMMC1. */
/* clang-format off */
#define BOARD_PINS(PIN) \
    PIN(HSE_IN,        H,  0, PIN_OSC) \
    PIN(HSE_OUT,       H,  1, PIN_OSC) \
    PIN(LSE_IN,        C, 14, PIN_OSC) \
    PIN(LSE_OUT,       C, 15, PIN_OSC) \
    PIN(SWDIO,         A, 13, 0) \
    PIN(SWCLK,         A, 14, 0) \
    PIN(SWO,           B,  3, 0) \
    PIN(UART_TX,       A,  9, 7) \
    PIN(UART_RX,       A, 10, 7) \
    PIN(KEY_ON,        A,  0, PIN_IN) \
    PIN(FMC_D0,        D, 14, 12) \
    PIN(FMC_D1,        D, 15, 12) \
    PIN(FMC_D2,        D,  0, 12) \
    PIN(FMC_D3,        D,  1, 12) \
    PIN(FMC_D4,        E,  7, 12) \
    PIN(FMC_D5,        E,  8, 12) \
    PIN(FMC_D6,        E,  9, 12) \
    PIN(FMC_D7,        E, 10, 12) \
    PIN(FMC_D8,        E, 11, 12) \
    PIN(FMC_D9,        E, 12, 12) \
    PIN(FMC_D10,       E, 13, 12) \
    PIN(FMC_D11,       E, 14, 12) \
    PIN(FMC_D12,       E, 15, 12) \
    PIN(FMC_D13,       D,  8, 12) \
    PIN(FMC_D14,       D,  9, 12) \
    PIN(FMC_D15,       D, 10, 12) \
    PIN(FMC_A0,        F,  0, 12) \
    PIN(FMC_A1,        F,  1, 12) \
    PIN(FMC_A2,        F,  2, 12) \
    PIN(FMC_A3,        F,  3, 12) \
    PIN(FMC_A4,        F,  4, 12) \
    PIN(FMC_A5,        F,  5, 12) \
    PIN(FMC_A6,        F, 12, 12) \
    PIN(FMC_A7,        F, 13, 12) \
    PIN(FMC_A8,        F, 14, 12) \
    PIN(FMC_A9,        F, 15, 12) \
    PIN(FMC_A10,       G,  0, 12) \
    PIN(FMC_A11,       G,  1, 12) \
    PIN(FMC_A12,       G,  2, 12) \
    PIN(FMC_BA0,       G,  4, 12) \
    PIN(FMC_BA1,       G,  5, 12) \
    PIN(FMC_NBL0,      E,  0, 12) \
    PIN(FMC_NBL1,      E,  1, 12) \
    PIN(FMC_SDCLK,     G,  8, 12) \
    PIN(FMC_SDNCAS,    G, 15, 12) \
    PIN(FMC_SDNRAS,    F, 11, 12) \
    PIN(FMC_SDNWE,     C,  0, 12) \
    PIN(FMC_SDCKE1,    B,  5, 12) \
    PIN(FMC_SDNE1,     B,  6, 12) \
    PIN(LCD_CS,        D,  7, 12) \
    PIN(LCD_RD,        D,  4, 12) \
    PIN(LCD_WR,        D,  5, 12) \
    PIN(LCD_DC,        D, 11, 12) \
    PIN(LCD_RESET,     D,  3, PIN_OUT) \
    PIN(LCD_TE,        G,  9, PIN_IN) \
    PIN(LCD_BL_DAC,    A,  4, PIN_AN) \
    PIN(QSPI_CLK,      B,  2, 9) \
    PIN(QSPI_NCS,      G,  6, 10) \
    PIN(QSPI_IO0,      F,  8, 10) \
    PIN(QSPI_IO1,      F,  9, 10) \
    PIN(QSPI_IO2,      F,  7, 9) \
    PIN(QSPI_IO3,      F,  6, 9) \
    PIN(SD_D0,         C,  8, 12) \
    PIN(SD_D1,         C,  9, 12) \
    PIN(SD_D2,         C, 10, 12) \
    PIN(SD_D3,         C, 11, 12) \
    PIN(SD_CK,         C, 12, 12) \
    PIN(SD_CMD,        D,  2, 12) \
    PIN(SD_DETECT,     G,  7, PIN_IN) \
    PIN(USB_DM,        A, 11, 10) \
    PIN(USB_DP,        A, 12, 10) \
    PIN(USB_VBUS_SENSE,A,  2, PIN_IN) \
    PIN(BUS_EN,        G,  3, PIN_OUT) \
    PIN(SD_EN,         G, 10, PIN_OUT) \
    PIN(VBAT_SENSE,    A,  3, PIN_AN) \
    PIN(VBAT_SENSE_EN, A,  1, PIN_OUT) \
    PIN(LED_DEBUG,     B,  8, PIN_OUT) \
    PIN(I2C_SCL,       B, 10, 4) \
    PIN(I2C_SDA,       B, 11, 4) \
    PIN(PMON_ALERT,    F, 10, PIN_IN) \
    PIN(MON_3V3_BUS,   A,  6, PIN_AN) \
    PIN(MON_3V3_SD,    C,  4, PIN_AN) \
    PIN(BL_SENSE,      C,  5, PIN_AN) \
    PIN(BL_SRC_3V3,    C, 13, PIN_OUT) \
    PIN(BL_SRC_VSYS,   D,  6, PIN_OUT) \
    PIN(DBG_TX2,       C,  6, 7) \
    PIN(DBG_RX2,       C,  7, 7) \
    PIN(DBG_MCO,       A,  8, 0) \
    PIN(DBG_IO0,       A, 15, PIN_OUT) \
    PIN(DBG_IO1,       B,  9, PIN_OUT) \
    PIN(DBG_IO2,       B, 15, PIN_OUT) \
    PIN(DBG_IO3,       A,  5, PIN_OUT) \
    PIN(DBG_IO4,       B,  7, PIN_OUT) \
    PIN(TP_SCL,        D, 12, 4) \
    PIN(TP_SDA,        D, 13, 4) \
    PIN(TP_INT,        C,  1, PIN_IN) \
    PIN(TP_RST,        A,  7, PIN_OUT) \
    PIN(KEY_ROW0,      G, 11, PIN_OD) \
    PIN(KEY_ROW1,      G, 12, PIN_OD) \
    PIN(KEY_ROW2,      G, 13, PIN_OD) \
    PIN(KEY_ROW3,      G, 14, PIN_OD) \
    PIN(KEY_ROW4,      B,  0, PIN_OD) \
    PIN(KEY_ROW5,      B,  1, PIN_OD) \
    PIN(KEY_ROW6,      B,  4, PIN_OD) \
    PIN(KEY_COL0,      E,  2, PIN_IN) \
    PIN(KEY_COL1,      E,  3, PIN_IN) \
    PIN(KEY_COL2,      E,  4, PIN_IN) \
    PIN(KEY_COL3,      E,  5, PIN_IN) \
    PIN(KEY_COL4,      E,  6, PIN_IN) \
    PIN(KEY_COL5,      B, 12, PIN_IN) \
    PIN(KEY_COL6,      B, 13, PIN_IN)
/* clang-format on */

/* Pin identifiers: P_<net> = (port index << 4) | pin, port A = 0 */
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 * the line (EXTI1, EXTI9_5, EXTI15_10). If the pin map moves one of these, the
 * asserts fail and point here: update the line, the vector/handler, and make
 * sure no key column (lines 2-6, 12, 13) uses the same number. */
#define EXTI_LINE_TP_INT     1  /* PC1  -> EXTI1_IRQHandler (touch_focaltech.c) */
#define EXTI_LINE_LCD_TE     9  /* PG9  -> EXTI9_5_IRQHandler (keypad.c -> lcd_te_irq) */
#define EXTI_LINE_PMON_ALERT 10 /* PF10 -> EXTI15_10_IRQHandler (keypad.c -> pmon_alert_irq) */
#define EXTI_LINE_KEY_ON     0  /* PA0  -> EXTI0 (wake from Stop) + WKUP1 (Standby) */
_Static_assert((P_TP_INT & 15) == EXTI_LINE_TP_INT, "TP_INT moved: update EXTI_LINE_TP_INT and its vector");
_Static_assert((P_LCD_TE & 15) == EXTI_LINE_LCD_TE, "LCD_TE moved: update EXTI_LINE_LCD_TE and its vector");
_Static_assert((P_PMON_ALERT & 15) == EXTI_LINE_PMON_ALERT, "PMON_ALERT moved: update EXTI_LINE_PMON_ALERT");
_Static_assert((P_KEY_ON & 15) == EXTI_LINE_KEY_ON && (P_KEY_ON >> 4) == PORT_IDX_A, "KEY_ON must stay PA0 (WKUP1)");
#define KEYCOL_LINE_CLASH(l) ((P_KEY_COL0 & 15) == (l) || (P_KEY_COL1 & 15) == (l) || (P_KEY_COL2 & 15) == (l) || \
                              (P_KEY_COL3 & 15) == (l) || (P_KEY_COL4 & 15) == (l) || (P_KEY_COL5 & 15) == (l) || \
                              (P_KEY_COL6 & 15) == (l))
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#define VBAT_DIV_RATIO  (147.0f / 47.0f) /* 100k over 47k */
#define RAIL_DIV_RATIO  2.0f             /* 100k / 100k */
#define BL_SENSE_OHMS   1.0f
/* Backlight sink setpoint: DAC1 (PA4, unbuffered, Ro 10-16 kohm) -> 10k -> BL_SET,
 * 1k to GND, 1 ohm sense: I_fs = 3.3 V * 1k / (10k + Ro + 1k) / 1 ohm. */
#define BL_DAC_FS_MA     (3300.0f * 1.0f / (10.0f + 13.0f + 1.0f)) /* ~138 mA nominal (Ro ~13k) */
#define BL_DAC_FS_MAX_MA (3300.0f * 1.0f / (10.0f + 10.0f + 1.0f)) /* ~157 mA worst case (Ro 10k): used
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/* default brightness: HAL_BACKLIGHT_DEFAULT_PCT (hal.h), 45 % = ~40 mA */
#define BL_MIN_DETECT_MA 2.0f   /* below this at the 20 mA probe: no panel / open LED string */
/* LED anode (LCD_A) supply selector (replaces solder jumper JP1), two P-FETs switched by N-FETs:
 *   BL_SRC_3V3  (PC13) high = 3V3_BUS -> LCD_A ON; low / released (100k pull-down) = off (reset default)
 *   BL_SRC_VSYS (PD6)  high = VSYS -> LCD_A ON; low / released (100k pull-down) = off (reset default)
 * Both paths are OFF at reset, in Standby and whenever the pins are analog (a pull-up on PC13 let a
 * reset while on VSYS overlap the two paths), so the firmware always drives PC13 high to use 3V3.
 * Never both on (VSYS would be tied to 3V3_BUS): backlight_src_switch() sets the LED current to 0,
 * turns the active path off, waits BL_SRC_DEAD_US (gate RC ~65 us), turns the other on, waits
 * BL_SRC_ON_US, restores the setpoint. PC13 is in the backup domain (RM0433 "PC13, PC14, PC15":
 * fed through the power switch, sinks <= 3 mA, <= 2 MHz / 30 pF, never a current source, RTC
 * tamper/OUT must not be routed to it): it only drives an N-FET gate at the lowest GPIO speed. */
#define BL_SRC_DEAD_US     1000u   /* both paths off */
#define BL_SRC_ON_US       200u    /* new path on, before the setpoint returns */
#define BL_SRC_SAT_FRAC    0.90f   /* on 3V3: measured < 90 % of the setpoint = saturated -> VSYS */
#define BL_SRC_BACK_FRAC   0.80f   /* on VSYS: setpoint < 80 % of the learned 3V3 limit -> 3V3 */
#define BL_SRC_MIN_MA      10.0f   /* below this setpoint 3V3_BUS always regulates: never checked */
#define BL_SRC_SETTLE_MS   5u      /* setpoint change -> BL_SENSE check */
#define BL_SRC_RECHECK_MS  2000u   /* periodic re-check on 3V3 (Vf drifts with temperature) */
#define BL_SRC_MIN_GAP_MS  500u    /* auto mode switches at most this often */
/* Touch controller: FocalTech FT6236 (FT6x36 family) on the panel FPC, powered
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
